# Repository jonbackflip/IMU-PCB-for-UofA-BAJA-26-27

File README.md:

A board containing the attitude and heading sensor (IMU) for the UofA BAJA's car. CAN circuitry contained on board alongside an Arduino Nano for UART communication to the IMU.

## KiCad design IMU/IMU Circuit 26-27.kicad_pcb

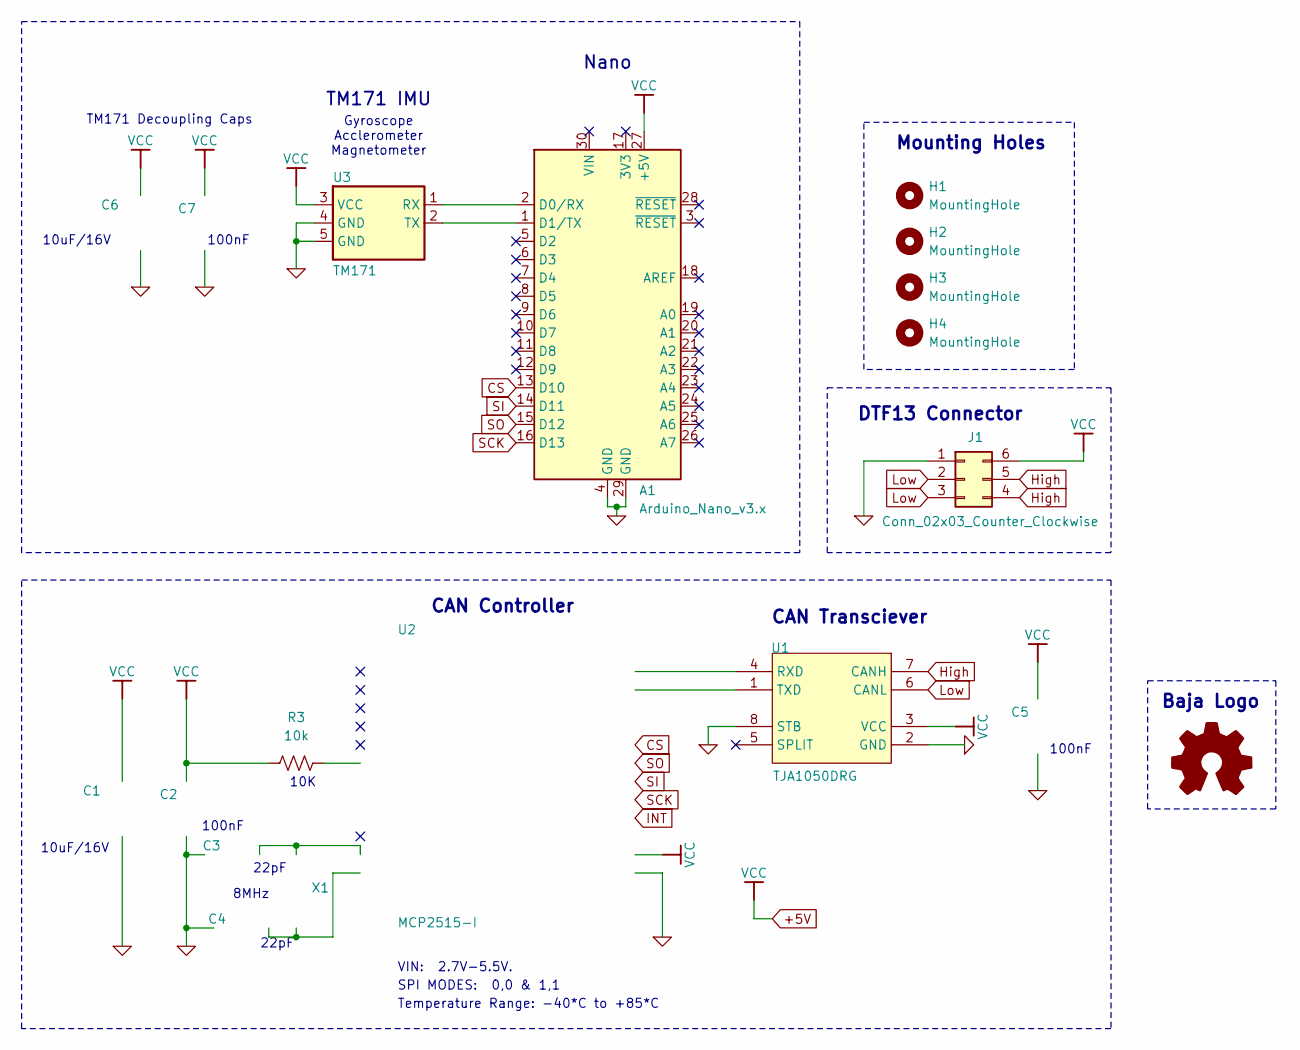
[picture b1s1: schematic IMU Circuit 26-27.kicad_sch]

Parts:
A1: Arduino_Nano_v3.x; Arduino_Nano
C1, C6: 10uF/16V; CP_Radial_Tantal_D5.0mm_P2.50mm
C2, C5, C7: 100nF; CP_Radial_D5.0mm_P2.50mm; PART NUMBER C0603-N.C.
C3, C4: 22pF; CP_Radial_D5.0mm_P2.50mm; PART NUMBER C0603-N.C.
H1, H2, H3, H4: MountingHole; MountingHole_3.2mm_M3
J1: Conn_02x03_Counter_Clockwise; TE_DTF13-6P
Logo1: Logo_Open_Hardware_Small; Baja Logo
R3: 10k; R_Axial_DIN0207_L6.3mm_D2.5mm_P5.08mm_Vertical
U1: TJA1050DRG; SOIC-8_5.3x5.3mm_P1.27mm; MANUFACTURER PART TJA1050DRG; LCSC PART NAME TJA1050DRG
U2: MCP2515-I; SOIC-18W_7.5x11.6mm_P1.27mm; MANUFACTURER PART MCP2515-I; JLCPCB PART CLASS Extended Part
U3: TM171; Transducer TM171
X1: 8MHz; Crystal_SMD_HC49-SD

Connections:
0: A1.4 (GND), A1.29 (GND), C1.2, C2.1, C3.2, C4.2, C5.1, C6.2, C7.1, J1.1, U1.2 (GND), U1.8 (STB), U2.9 (VSS), U3.4 (GND), U3.5 (GND)
+5V: A1.27 (+5V), C1.1, C2.2, C5.2, C6.1, C7.2, J1.6, R3.1, U1.3 (VCC), U2.18 (VDD), U3.3 (VCC)
CS: A1.13 (D10), U2.16 (~CS)
High: J1.4, J1.5, U1.7 (CANH)
INT: U2.12 (~INT)
Low: J1.2, J1.3, U1.6 (CANL)
unnamed: A1.2 (D0/RX), U3.1 (RX)
unnamed: A1.1 (D1/TX), U3.2 (TX)
unnamed: U1.4 (RXD), U2.2 (RXCAN)
unnamed: U1.1 (TXD), U2.1 (TXCAN)
unnamed: C4.1, U2.8 (OSC1), X1.1
unnamed: C3.1, U2.7 (OSC2), X1.2
unnamed: R3.2, U2.17 (~RESET)
SCK: A1.16 (D13), U2.13 (SCK)
SI: A1.14 (D11), U2.14 (SI)
SO: A1.15 (D12), U2.15 (SO)

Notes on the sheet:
10K
100nF
Temperature Range: -40*C to +85*C
22pF
10uF/16V
CAN Controller
8MHz
TM171 Decoupling Caps
Nano
TM171 IMU
DTF13 Connector
SPI MODES: 0,0 & 1,1
Baja Logo
CAN Transciever
Gyroscope Acclerometer Magnetometer
Mounting Holes
VIN: 2.7V-5.5V.

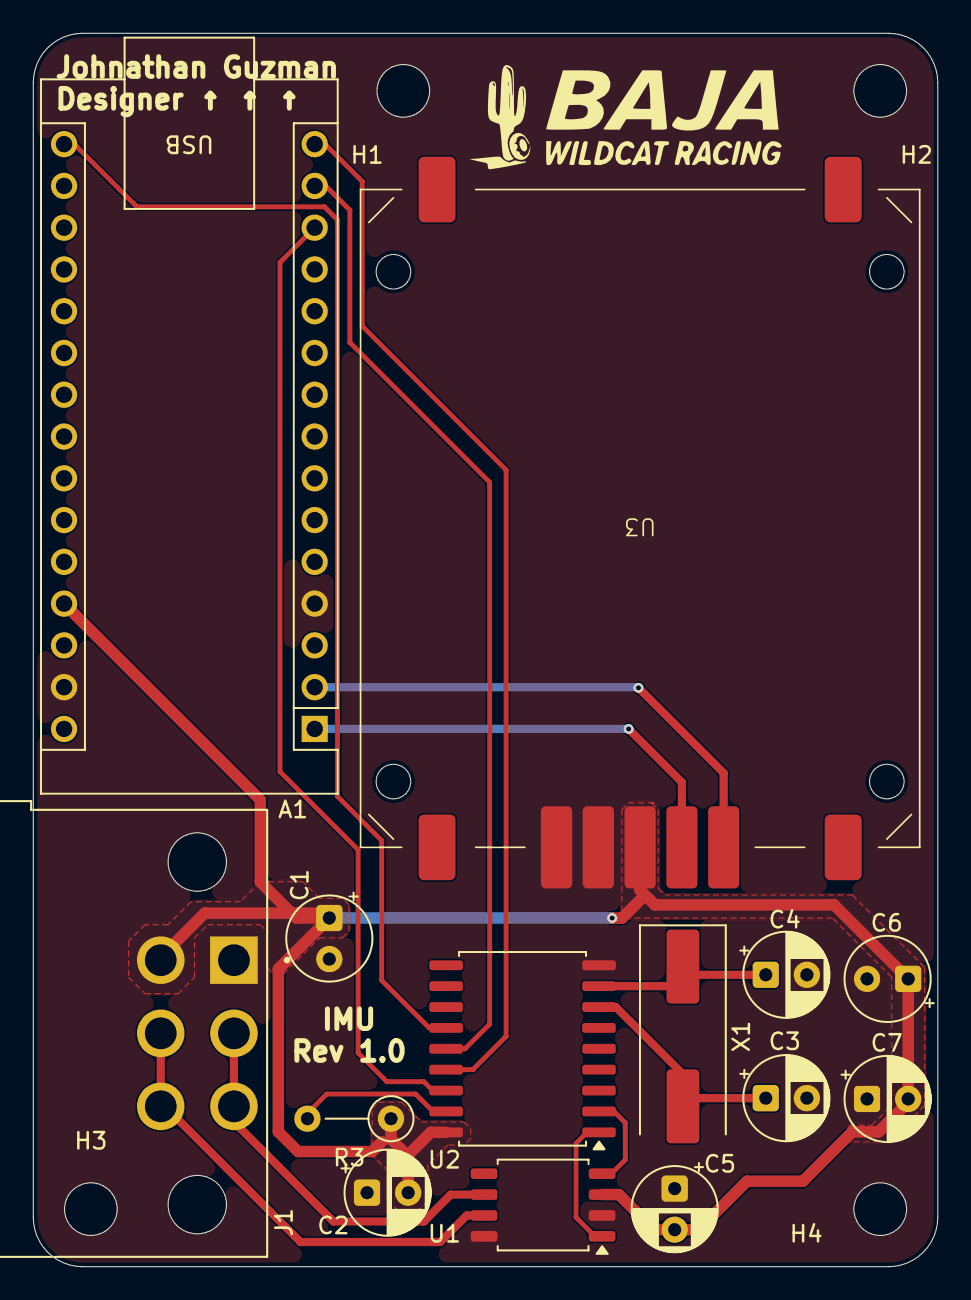
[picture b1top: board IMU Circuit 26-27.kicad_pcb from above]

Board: 2 copper layers, 55.0 x 75.0 mm, 18 parts (0 on the bottom side), 15 nets.
